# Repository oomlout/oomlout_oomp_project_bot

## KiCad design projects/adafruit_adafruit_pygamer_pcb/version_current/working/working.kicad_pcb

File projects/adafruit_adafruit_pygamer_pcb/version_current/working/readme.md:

# OOMP Project  
## Adafruit-PyGamer-PCB  by adafruit  
  
oomp key: oomp_projects_flat_adafruit_adafruit_pygamer_pcb  
(snippet of original readme)  
  
- Adafruit-PyGamer-PCB  
PCB files for Adafruit PyGamer  
  
Format is EagleCAD schematic and board layout  
  
For more details, check out the product page at  
  
   * https://www.adafruit.com/product/4242  
  
Adafruit invests time and resources providing this open source design,   
please support Adafruit and open-source hardware by purchasing   
products from Adafruit!  
  
Designed by Adafruit Industries.    
Creative Commons Attribution, Share-Alike license, check license.txt for more information  
All text above must be included in any redistribution  
  
  full source readme at [readme_src.md](readme_src.md)  
  
source repo at: [https://github.com/adafruit/Adafruit-PyGamer-PCB](https://github.com/adafruit/Adafruit-PyGamer-PCB)  
## Board  

## Schematic  

[schematic pdf](working_schematic.pdf)  
## Images

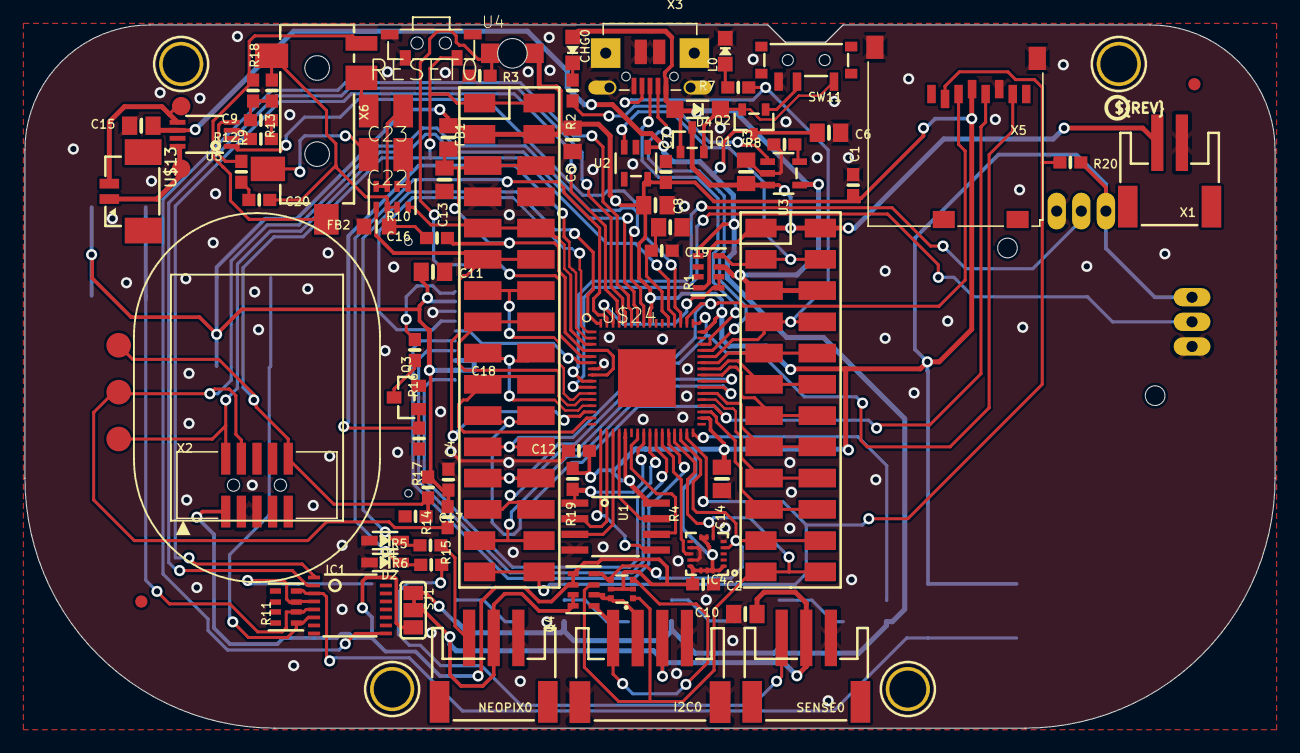
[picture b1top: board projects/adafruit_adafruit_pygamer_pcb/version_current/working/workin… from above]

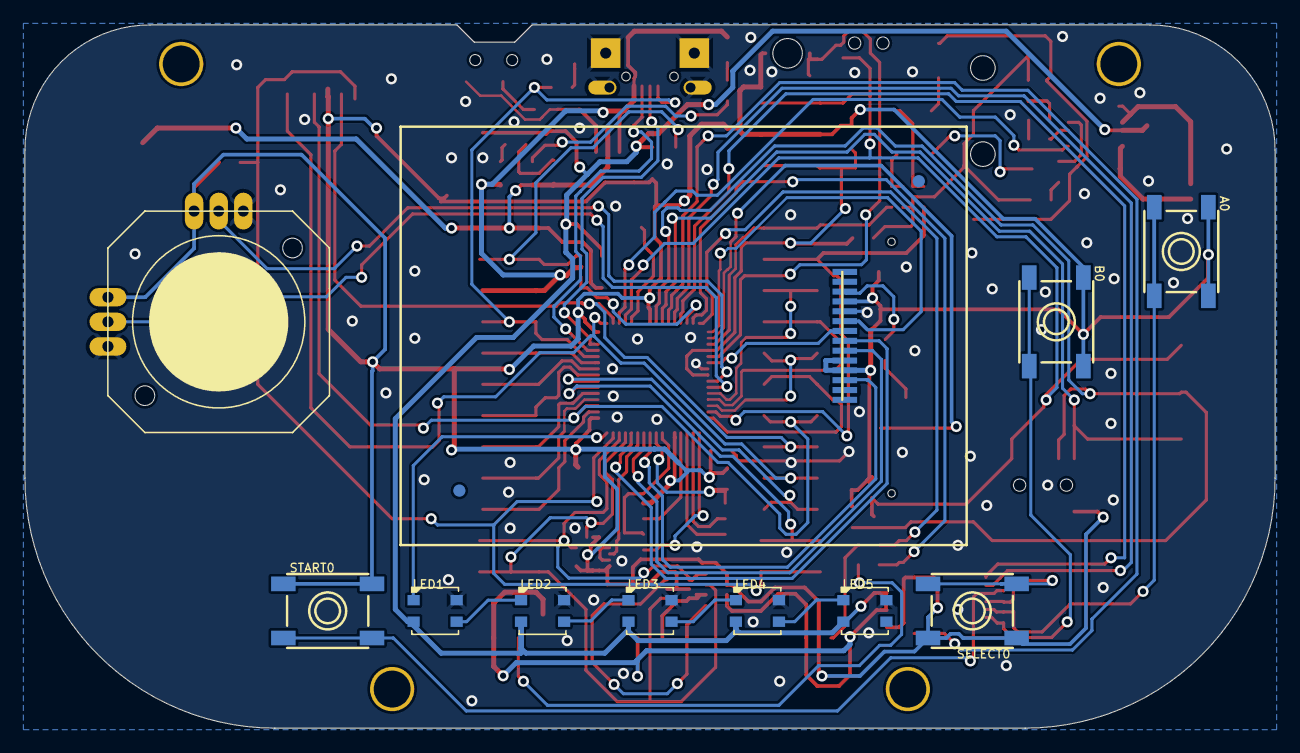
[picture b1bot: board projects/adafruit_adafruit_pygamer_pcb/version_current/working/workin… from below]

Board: 2 copper layers, 101.6 x 57.1 mm, 102 parts (14 on the bottom side), 92 nets.

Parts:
A0: 6MM_SMT_6MMCAP
B0: 6MM_SMT_6MMCAP
C1, C2, C4, C7, C9, C12, C16, C19, C20: 1uF; 0603-NO
C3, C6, C8: 10µF; 0805-NO
C5, C10, C11, C13, C14, C15, C18: 10uF; 0805-NO
C17: 0.1uF; 0603-NO
C22, C23: 100uF; C1210
CHG0: ORANGE; CHIPLED_0805_NOOUTLINE
D1, D2: 3.6V; SOD-323
D4: MBR0540; SOD-123
FB1: Ferrite; 0805-NO
FB2: Ferrite; _0805MP
I2C0: JST PH 4; JSTPH4
IC1: 74165TSSOP; TSSOP16
IC4: LIS3DH; LGA16_3X3MM
JOY1: JOYSTICK_ANALOG_XY; JOYSTICK_ANALOG_MINITHM
L0: RED; CHIPLED_0805_NOOUTLINE
LCD1: DISP_LCD_JDT1800; JD-T1800
LED1, LED2, LED3, LED4, LED5: WS2812B3535; LED3535
MS1: FEATHERWING_SMTDUALNOHOLES; FEATHERWING_SMT_NOHOLES
NEOPIX0: JST PH 3; JSTPH3
Q1, Q2: DMG2305; SOT23-R
Q3: BSS138; SOT23-WIDE
Q4: BSS138; SOT363
R1, R11: 100K; RESPACK_4X0603
R2, R5, R6: 1K; 0603-NO
R3, R14, R15, R20: 10K; 0603-NO
R4: 10K; RESPACK_4X0603
R7, R13, R18: 2.2K; 0603-NO
R8: 4.7K; 0603-NO
R9, R12: 100; 0603-NO
R10: 100; RESPACK_4X0603
R16: 10; 0603-NO
R17, R19: 100K; 0603-NO
RESET0: SPST_TACTILE_RA
SELECT0: 6MM_SMT_6MMCAP
SENSE0: JST PH 3; JSTPH3
SJ1: SOLDERJUMPER_2WAY_OPEN_NOPASTE
START0: 6MM_SMT_6MMCAP
SW11: SPDT_SMT_SSSS811101
TP1, TP2: TESTPOINT_ROUND_1.5MM_NO
TP6, TP7, TP8: TESTPOINT_ROUND_2MM_NO
U1: GD25Q64; SOIC8_208MIL
U2: AP2112-3.3; SOT23-5
U3: MCP73831T-2ACI/OT; SOT23-5
U4: ALS-PT21; ALS-PT26-21C
U5: PAM8302AASCR; MSOP8_0.65MM
U$5, U$6, U$17, U$18: MOUNTINGHOLE3.0THIN; MOUNTINGHOLE_3.0_PLATEDTHIN
U$8: SPEAKER_OVAL8OHM
U$13: CON_MOLEX_2P; 53398-0271
U$24: ATSAMD51J19; PQFN64-1
U$34, U$35, U$43, U$46: FIDUCIAL_1MM
U$37: PCBFEAT-REV-040
U$47: PYGAMER_BACK
U$48: PYGAMER_FRONT
X1: JSTPH; JSTPH2
X2: 2x5 0.05" SWD; 2X05_1.27MM_BOX_POSTS
X3: microUSB; 4UCONN_20329_V2
X5: MicroSD; MICROSD
X6: 4UCONN_19269

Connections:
+3V3: A0.B, A0.B', B0.B, B0.B', C1.1, C2.1, C4.1, C5.1, C7.1, C8.1, C11.1, C12.1, C14.1, FB1.1, IC1.16, IC4.1, IC4.7, IC4.8, IC4.13, IC4.14, IC4.15, IC4.16, JOY1.X+, JOY1.Y+, LCD1.4, LCD1.10, LCD1.11, MS1.2, MS1.2B, Q4.2, Q4.5, R4.1, R4.2, R14.1, R15.1, R19.1, R20.2, SELECT0.B, SELECT0.B', SJ1.3, START0.B, START0.B', U1.8, U2.5, U4.2_C, U$24.21, U$24.34, U$24.48, U$24.56, X2.1, X5.4
A0: MS1.5, MS1.5B, R10.8, U$24.3
A1: MS1.6, MS1.6B, R10.5, U$24.14
A2: MS1.7, MS1.7B, U$24.11
A3: MS1.8, MS1.8B, U$24.12
A4: MS1.9, MS1.9B, U$24.13
A5: MS1.10, MS1.10B, U$24.15
A6_VMEAS: R1.1, R1.2, U$24.62
A7_LIGHT: R3.2, U4.1_E, U$24.5
AGND: C16.2, C20.2, FB2.1, R10.6, R10.7, R13.1, X6.1
AVCC: C13.1, C16.1, FB1.2, MS1.3, MS1.3B, U$24.4, U$24.8
BUTTON4: IC1.3, R11.4, START0.A, START0.A'
BUTTON5: IC1.4, R11.3, SELECT0.A, SELECT0.A'
BUTTON6: A0.A, A0.A', IC1.5, R11.2
BUTTON7: B0.A, B0.A', IC1.6, R11.1
BUTTON_CLK: IC1.2, U$24.60
BUTTON_LATCH: IC1.1, U$24.61
BUTTON_OUT: IC1.9, U$24.59
CHG_LED: R2.2, U3.1
CHG_RATE: R8.1, U3.5
D2_: NEOPIX0.3, R5.1
D2_A8: D1.C, R5.2, U$24.64
D3_: R6.1, SENSE0.3
D3_A9: D2.C, R6.2, U$24.63
D4_SDCS: MS1.16, MS1.16B, R20.1, U$24.31, X5.2
D5: MS1.19, MS1.19B, U$24.35
D6: MS1.20, MS1.20B, U$24.37
D7_LISIRQ: IC4.11, U$24.27
D8_NEOPIX: LED1.1, U$24.32
D9: MS1.21, MS1.21B, U$24.38
D10: MS1.22, MS1.22B, U$24.41
D11: MS1.23, MS1.23B, U$24.42
D12: MS1.24, MS1.24B, U$24.43
D13_JACDAC: MS1.25, MS1.25B, R7.1, U$24.44, X3.ID
D+: U$24.46, X3.D+
D-: U$24.45, X3.D-
EN: MS1.27, MS1.27B, R1.4, U2.3
GND: C1.2, C2.2, C3.2, C4.2, C5.2, C6.2, C7.2, C8.2, C10.2, C11.2, C12.2, C13.2, C14.2, C15.2, C17.1, C18.2, C19.2, D1.A, D2.A, FB2.2, I2C0.1, I2C0.NC1, I2C0.NC2, IC1.8, IC1.10, IC1.11, IC1.12, IC1.13, IC1.14, IC1.15, IC4.5, IC4.10, IC4.12, JOY1.X-, JOY1.Y-, L0.C, LCD1.2, LCD1.5, LCD1.13, LED1.4, LED2.4, LED3.4, LED4.4, LED5.4, MS1.4, MS1.4B, NEOPIX0.1, Q3.2, R1.6, R1.7, R3.1, R8.2, R11.5, R11.6, R11.7, R11.8, R17.2, RESET0.2, RESET0.MT1, RESET0.MT2, SENSE0.1, SW11.C, U1.4, U2.2, U3.2, U5.7, U$24.7, U$24.22, U$24.33, U$24.47, U$24.54, U$24.EXP, X1.1, X2.3, X2.5, X3.BASE@1, X3.BASE@2, X3.GND, X3.SPRT@1, X3.SPRT@2, X3.SPRT@3, X3.SPRT@4, X5.6, X5.MT1, X5.MT2
JOYX: JOY1.X, U$24.10
JOYY: JOY1.Y, U$24.9
LEDK: LCD1.3, R16.1
MISO: MS1.13, MS1.13B, U$24.49, X5.7
MOSI: MS1.12, MS1.12B, U$24.50, X5.3
unnamed: CHG0.C, R2.1
unnamed: L0.A, R7.2
unnamed: LED1.3, LED2.1
unnamed: LED2.3, LED3.1
unnamed: LED3.3, LED4.1
unnamed: Q3.3, R16.2
unnamed: LED4.3, LED5.1
unnamed: D4.C, Q1.2, Q2.2, SW11.A
unnamed: R9.2, U5.4
unnamed: R12.2, U5.3
unnamed: C23.2, X6.3
unnamed: C9.2, R13.2, R18.1
unnamed: C22.2, X6.2
unnamed: C23.1, R10.3, R10.4
unnamed: C20.1, R9.1
unnamed: C9.1, R12.1
unnamed: C22.1, R10.1, R10.2
ON/OFF: Q2.1, SW11.B
QSPI_CS: R19.2, U1.1, U$24.24
QSPI_DATA[0]: U1.5, U$24.17
QSPI_DATA[1]: U1.2, U$24.18
QSPI_DATA[2]: U1.3, U$24.19
QSPI_DATA[3]: U1.7, U$24.20
QSPI_SCK: U1.6, U$24.23
RX: MS1.14, MS1.14B, U$24.40
SCK: MS1.11, MS1.11B, U$24.36, X5.5
SCL: I2C0.4, Q4.3, R4.5
SCL_3V: IC4.4, MS1.18, MS1.18B, Q4.4, R4.8, U$24.30
SDA: I2C0.3, Q4.6, R4.6
SDA_3V: IC4.6, MS1.17, MS1.17B, Q4.1, R4.7, U$24.29
SPEAKER_IN: R18.2, X6.4, X6.5
SPKR+: TP1.P$1, U5.5, U$13.2
SPKR-: TP2.P$1, U5.8, U$13.1
SPKR_EN: U5.1, U$24.51
SWCLK: R15.2, TP6.P$1, U$24.57, X2.4
SWDIO: TP7.P$1, U$24.58, X2.2
TFT_CS: LCD1.12, U$24.25
TFT_DC: LCD1.7, U$24.6
TFT_LITE: Q3.1, R17.1, U$24.2
TFT_MOSI: LCD1.8, U$24.28
TFT_RST: LCD1.6, U$24.1
TFT_SCK: LCD1.9, U$24.26
TX: MS1.15, MS1.15B, U$24.39
V+: C6.1, C15.1, LED1.2, LED2.2, LED3.2, LED4.2, LED5.2, Q2.3, R1.5, SJ1.1, U2.1, U5.6
VBAT: C3.1, MS1.28, MS1.28B, Q1.3, R1.8, U3.3, X1.2
VBUS: CHG0.A, D4.A, MS1.26, MS1.26B, Q1.1, R1.3, U3.4, X3.VBUS
VCC: C10.1, I2C0.2, NEOPIX0.2, R4.3, R4.4, SENSE0.2, SJ1.2
VDDCORE2: C18.1, C19.1, U$24.53
~RESET: C17.2, MS1.1, MS1.1B, R14.2, RESET0.1, TP8.P$1, U$24.52, X2.10

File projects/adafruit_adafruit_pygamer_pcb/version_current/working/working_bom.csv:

"Id";"Designator";"Footprint";"Quantity";"Designation";"Supplier and ref";
1;"C11,C13,C5,C10,C15,C14,C18";"0805-NO";7;"10uF";;;
2;"C12,C4,C2,C20,C16,C19,C9,C7,C1";"0603-NO";9;"1uF";;;
3;"R3,R14,R15,R20";"0603-NO";4;"10K";;;
4;"IC4";"LGA16_3X3MM";1;"LIS3DH";;;
5;"R8";"0603-NO";1;"4.7K";;;
6;"FB2";"_0805MP";1;"Ferrite";;;
7;"U$24";"PQFN64-1";1;"ATSAMD51J19";;;
8;"IC1";"TSSOP16";1;"74165TSSOP";;;
9;"SENSE0,NEOPIX0";"JSTPH3";2;"JST PH 3";;;
10;"C22,C23";"C1210";2;"100uF";;;
11;"R17,R19";"0603-NO";2;"100K";;;
12;"Q2,Q1";"SOT23-R";2;"DMG2305";;;
13;"R13,R7,R18";"0603-NO";3;"2.2K";;;
14;"U$13";"53398-0271";1;"CON_MOLEX_2P";;;
15;"FB1";"0805-NO";1;"Ferrite";;;
16;"U2";"SOT23-5";1;"AP2112-3.3";;;
17;"U$47";"PYGAMER_BACK";1;"";;;
18;"TP7,TP6,TP8";"TESTPOINT_ROUND_2MM_NO";3;"";;;
19;"R10";"RESPACK_4X0603";1;"100";;;
20;"R9,R12";"0603-NO";2;"100";;;
21;"D1,D2";"SOD-323";2;"3.6V";;;
22;"I2C0";"JSTPH4";1;"JST PH 4";;;
23;"Q4";"SOT363";1;"BSS138";;;
24;"D4";"SOD-123";1;"MBR0540";;;
25;"C3,C8,C6";"0805-NO";3;"10µF";;;
26;"U$35,U$34,U$43,U$46";"FIDUCIAL_1MM";4;"FIDUCIAL_1MM";;;
27;"X2";"2X05_1.27MM_BOX_POSTS";1;"2x5 0.05" SWD";;;
28;"R2,R5,R6";"0603-NO";3;"1K";;;
29;"U4";"ALS-PT26-21C";1;"ALS-PT21";;;
30;"L0";"CHIPLED_0805_NOOUTLINE";1;"RED";;;
31;"TP2,TP1";"TESTPOINT_ROUND_1.5MM_NO";2;"";;;
32;"C17";"0603-NO";1;"0.1uF";;;
33;"U5";"MSOP8_0.65MM";1;"PAM8302AASCR";;;
34;"U$6,U$18,U$5,U$17";"MOUNTINGHOLE_3.0_PLATEDTHIN";4;"MOUNTINGHOLE3.0THIN";;;
35;"U1";"SOIC8_208MIL";1;"GD25Q64";;;
36;"SJ1";"SOLDERJUMPER_2WAY_OPEN_NOPASTE";1;"";;;
37;"U$8";"SPEAKER_OVAL8OHM";1;"";;;
38;"X3";"4UCONN_20329_V2";1;"microUSB";;;
39;"SW11";"SPDT_SMT_SSSS811101";1;"";;;
40;"MS1";"FEATHERWING_SMT_NOHOLES";1;"FEATHERWING_SMTDUALNOHOLES";;;
41;"R16";"0603-NO";1;"10";;;
42;"X6";"4UCONN_19269";1;"";;;
43;"X5";"MICROSD";1;"MicroSD";;;
44;"R1,R11";"RESPACK_4X0603";2;"100K";;;
45;"RESET0";"SPST_TACTILE_RA";1;"";;;
46;"X1";"JSTPH2";1;"JSTPH";;;
47;"U3";"SOT23-5";1;"MCP73831T-2ACI/OT";;;
48;"CHG0";"CHIPLED_0805_NOOUTLINE";1;"ORANGE";;;
49;"U$37";"PCBFEAT-REV-040";1;"";;;
50;"Q3";"SOT23-WIDE";1;"BSS138";;;
51;"R4";"RESPACK_4X0603";1;"10K";;;
52;"START0,SELECT0,B0,A0";"6MM_SMT_6MMCAP";4;"";;;
53;"LED5,LED2,LED1,LED3,LED4";"LED3535";5;"WS2812B3535";;;
54;"LCD1";"JD-T1800";1;"DISP_LCD_JDT1800";;;
55;"JOY1";"JOYSTICK_ANALOG_MINITHM";1;"JOYSTICK_ANALOG_XY";;;
56;"U$48";"PYGAMER_FRONT";1;"";;;

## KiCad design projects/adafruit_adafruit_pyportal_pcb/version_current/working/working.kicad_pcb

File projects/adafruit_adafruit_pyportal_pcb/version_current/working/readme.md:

# Adafruit-PyPortal-PCB by adafruit  
This is a harvested standardized copy of a project from github.  
The original project can be found at:  
https://github.com/adafruit/Adafruit-PyPortal-PCB  
Please consult that link for additional, details, files, and license information.  
Note: It was auto harvested and if the original repo had more than one board file or anything out of the ordinary the files here are likely not representative.

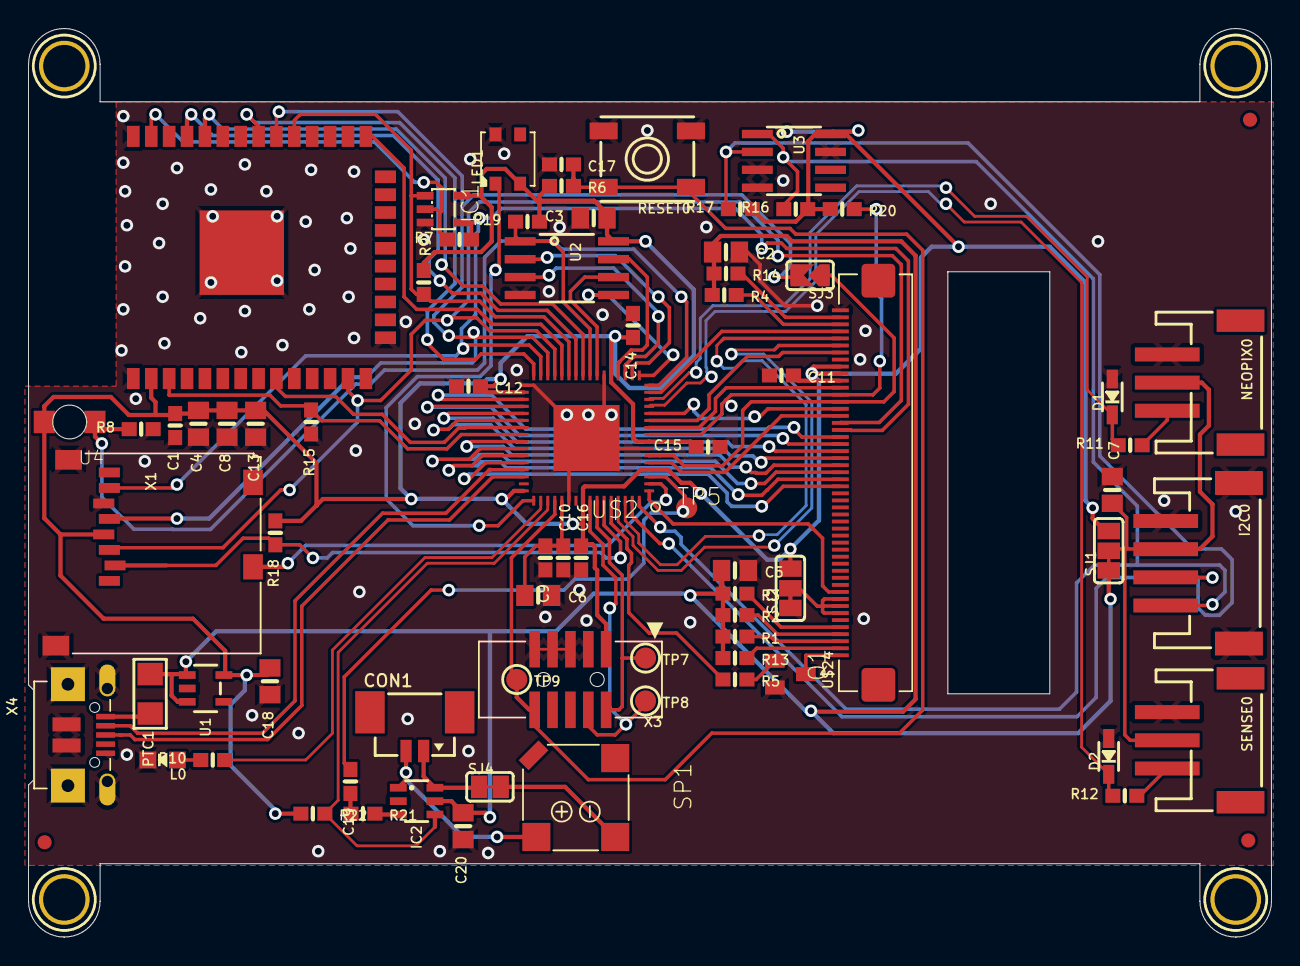
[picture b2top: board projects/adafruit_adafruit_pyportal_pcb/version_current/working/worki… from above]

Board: 16 copper layers, 88.3 x 64.5 mm, 81 parts (1 on the bottom side), 75 nets.

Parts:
C1, C17, C19: 0.1uF; 0603-NO
C2, C3, C5, C6, C7, C8, C13, C18, C20: 10uF; 0805-NO
C4: 0.1uF; 0805-NO
C9: 1uF; 0603-NO
C10, C11, C12, C14, C15, C16: .1u; 0603-NO
CON1: CON_MOLEX_2P; 53398-0271
D1, D2: 3.6V; SOD-323
I2C0: JST PH 4; JSTPH4
IC1: 74AHC1G125; SOT23-5L
IC2: PAM8301; SOT23-6
L0: RED; CHIPLED_0805_NOOUTLINE
LED1: WS2812B3535; LED3535
NEOPIX0: JST PH 3; JSTPH3
PTC1: 500mA; 1206
Q1: MMBT2222; SOT23-BEC
R1, R2, R3, R4, R13, R14: 100; 0603-NO
R5, R10, R11, R12: 1K; 0603-NO
R6, R8, R9, R15, R16, R17, R18, R19, R20: 10K; 0603-NO
R7: DNP; 0603-NO
R21, R22: 47K; 0603-NO
RESET0: EVQQ 6mm; EVQ-Q2_SMALLER
SENSE0: JST PH 3; JSTPH3
SJ1, SJ2: SOLDERJUMPER_2WAY_OPEN_NOPASTE
SJ3: SOLDERJUMPER_ARROW_NOPASTE
SJ4: SOLDERJUMPER_CLOSEDWIRE
SP1: 7.5mm SPK; BUZZER_SMT_7.5MM
TP5: TPTP15R; TP15R
TP7, TP8, TP9: TESTPOINT_ROUND_1.5MM
U1: AP2112-3.3; SOT23-5
U2: GD25Q64; SOIC8_208MIL
U3: ADT7410; SOIC8_150MIL
U4: ALS-PT21; ALS-PT26-21C
U$2: ATSAMD51J20; PQFN64-1
U$7, U$15, U$16, U$17: MOUNTINGHOLE3.0THIN; MOUNTINGHOLE_3.0_PLATEDTHIN
U$9, U$11, U$23: FIDUCIAL_1MM
U$24: DISP_LCD_6LED_240X320_50PIN; TFT_3.2IN_240X320_50PIN
X1: microSD; MICROSD
X3: 2x5 0.05" SWD; 2X05_1.27MM_BOX_POSTS
X4: microUSB; 4UCONN_20329_V2
X6: ESP32_WROOM32; WROOM32

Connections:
3.3V: C1.1, C3.1, C4.1, C8.1, C11.2, C12.2, C13.1, C14.2, C15.2, C16.2, C18.1, IC1.5, LED1.2, R6.1, R9.2, R16.1, R17.1, R18.1, R19.1, R20.1, R22.1, SJ1.3, SJ2.3, U1.5, U2.8, U3.8, U4.2_C, U$2.4, U$2.8, U$2.21, U$2.34, U$2.48, U$2.56, U$24.40, U$24.41, U$24.42, X1.4, X3.1, X6.2
+5V: C2.1, C5.1, C20.1, IC2.5, PTC1.1, R1.1, R2.1, R3.1, R4.1, R13.1, R14.1, SJ1.1, U1.1, U1.3
AUDIO_OUT: C19.1, TP5.TP, U$2.3
CARDDET: U$2.2, X1.CD2
D3: R12.1, SENSE0.3
D3_UNSAFE: D2.C, R12.2, U$2.13
D4: NEOPIX0.3, R11.1
D4_UNSAFE: D1.C, R11.2, U$2.14
D13: R10.1, U$2.50
D+: U$2.46, X4.D+
D-: U$2.45, X4.D-
ESP_BUSY: U$2.39, X6.9
ESP_CS: IC1.1, R9.1, U$2.27, X6.29
ESP_GPIO0: U$2.28, X6.25
ESP_MISO: IC1.2, R7.2, X6.37
ESP_RESET: R15.1, U$2.40, X6.3
ESP_RTS: U$2.32, X6.31
GND: C1.2, C2.2, C3.2, C4.2, C5.2, C6.2, C7.2, C8.2, C9.2, C10.1, C11.1, C12.1, C13.2, C14.1, C15.1, C16.1, C17.1, C18.2, C20.2, D1.A, D2.A, I2C0.1, I2C0.NC1, I2C0.NC2, IC1.3, IC2.2, L0.C, LED1.4, NEOPIX0.1, Q1.E, R8.1, R15.2, RESET0.A, RESET0.A', SENSE0.1, SJ2.1, U1.2, U2.4, U3.3, U3.4, U3.7, U$2.7, U$2.22, U$2.33, U$2.47, U$2.54, U$2.EXP, U$24.6, U$24.43, U$24.50, X1.6, X1.MT1, X1.MT2, X3.3, X3.5, X3.7, X3.9, X4.BASE@1, X4.BASE@2, X4.GND, X4.SPRT@1, X4.SPRT@2, X4.SPRT@3, X4.SPRT@4, X6.1, X6.15, X6.38, X6.P$1
LCD_DATA0: U$2.35, U$24.32
LCD_DATA1: U$2.36, U$24.31
LCD_DATA2: U$2.37, U$24.30
LCD_DATA3: U$2.38, U$24.29
LCD_DATA4: U$2.41, U$24.28
LCD_DATA5: U$2.42, U$24.27
LCD_DATA6: U$2.43, U$24.26
LCD_DATA7: U$2.44, U$24.25
LEDK: Q1.C, U$24.1
LIGHT: R8.2, U4.1_E, U$2.16
MISO: IC1.4, R7.1, U$2.31, U$24.33, X1.7
MOSI: U$2.29, U$24.34, X1.3, X6.13
unnamed: R4.2, U$24.48
unnamed: R1.2, U$24.3
unnamed: R2.2, U$24.4
unnamed: R3.2, U$24.5
unnamed: SJ2.2, U$24.7, U$24.8, U$24.9
unnamed: R14.2, U$24.49
unnamed: R13.2, U$24.2
unnamed: L0.A, R10.2
unnamed: C19.2, R21.1
unnamed: IC2.3, R21.2
unnamed: SJ4.2, SP1.-
unnamed: Q1.B, R5.2
NEOPIX: LED1.1, U$2.49
QSPI_CS: R19.2, U2.1, U$2.24
QSPI_DATA[0]: U2.5, U$2.17
QSPI_DATA[1]: U2.2, U$2.18
QSPI_DATA[2]: U2.3, U$2.19
QSPI_DATA[3]: U2.7, U$2.20
QSPI_SCK: U2.6, U$2.23
RXD: U$2.26, X6.35
SCK: SJ3.2, U$2.30, X1.5, X6.30
SCL: I2C0.4, R16.2, U3.1, U$2.64
SDA: I2C0.3, R17.2, U3.2, U$2.63
SD_CS: R18.2, U$2.59, X1.2
SPKR+: CON1.2, IC2.1, SP1.+
SPK_SD: IC2.4, R22.2, U$2.51
SPRK-: CON1.1, IC2.6, SJ4.1
SWCLK: TP8.P$1, U$2.57, X3.4
SWDIO: TP7.P$1, U$2.58, X3.2
TFT_BACKLITE: R5.1, U$2.60
TFT_CS: R20.2, U$2.9, U$24.38
TFT_RD: U$2.5, U$24.35
TFT_RESET: U$2.1, U$24.10
TFT_RS: SJ3.1, U$2.6, U$24.37
TFT_TE: U$2.10, U$24.39
TFT_WR: U$2.12, U$24.36
TOUCH_XL: U$2.62, U$24.46
TOUCH_XR: U$2.11, U$24.44
TOUCH_YD: U$2.61, U$24.45
TOUCH_YU: U$2.15, U$24.47
TXD: U$2.25, X6.34
VBUS: PTC1.2, X4.VBUS
VCC: C7.1, I2C0.2, NEOPIX0.2, SENSE0.2, SJ1.2
VDDCORE: C6.1, C9.1, C10.2, U$2.53
~RESET: C17.2, R6.2, RESET0.B, RESET0.B', TP9.P$1, U$2.52, X3.10

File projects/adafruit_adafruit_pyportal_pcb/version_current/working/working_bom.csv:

"Id";"Designator";"Footprint";"Quantity";"Designation";"Supplier and ref";
1;"IC2";"SOT23-6";1;"PAM8301";;;
2;"C7,C5,C8,C3,C13,C18,C6,C20,C2";"0805-NO";9;"10uF";;;
3;"SP1";"BUZZER_SMT_7.5MM";1;"7.5mm SPK";;;
4;"C12,C14,C11,C10,C15,C16";"0603-NO";6;".1u";;;
5;"R8,R15,R20,R19,R6,R9,R17,R16,R18";"0603-NO";9;"10K";;;
6;"TP8,TP7,TP9";"TESTPOINT_ROUND_1.5MM";3;"";;;
7;"NEOPIX0,SENSE0";"JSTPH3";2;"JST PH 3";;;
8;"C9";"0603-NO";1;"1uF";;;
9;"R2,R4,R14,R13,R3,R1";"0603-NO";6;"100";;;
10;"L0";"CHIPLED_0805_NOOUTLINE";1;"RED";;;
11;"C4";"0805-NO";1;"0.1uF";;;
12;"U$17,U$15,U$16,U$7";"MOUNTINGHOLE_3.0_PLATEDTHIN";4;"MOUNTINGHOLE3.0THIN";;;
13;"I2C0";"JSTPH4";1;"JST PH 4";;;
14;"D1,D2";"SOD-323";2;"3.6V";;;
15;"X6";"WROOM32";1;"ESP32_WROOM32";;;
16;"C17,C19,C1";"0603-NO";3;"0.1uF";;;
17;"U$11,U$23,U$9";"FIDUCIAL_1MM";3;"FIDUCIAL_1MM";;;
18;"U3";"SOIC8_150MIL";1;"ADT7410";;;
19;"R5,R11,R12,R10";"0603-NO";4;"1K";;;
20;"TP5";"TP15R";1;"TPTP15R";;;
21;"R7";"0603-NO";1;"DNP";;;
22;"RESET0";"EVQ-Q2_SMALLER";1;"EVQQ 6mm";;;
23;"X1";"MICROSD";1;"microSD";;;
24;"U$2";"PQFN64-1";1;"ATSAMD51J20";;;
25;"SJ4";"SOLDERJUMPER_CLOSEDWIRE";1;"";;;
26;"X3";"2X05_1.27MM_BOX_POSTS";1;"2x5 0.05" SWD";;;
27;"R21,R22";"0603-NO";2;"47K";;;
28;"SJ3";"SOLDERJUMPER_ARROW_NOPASTE";1;"";;;
29;"CON1";"53398-0271";1;"CON_MOLEX_2P";;;
30;"SJ2,SJ1";"SOLDERJUMPER_2WAY_OPEN_NOPASTE";2;"";;;
31;"U2";"SOIC8_208MIL";1;"GD25Q64";;;
32;"Q1";"SOT23-BEC";1;"MMBT2222";;;
33;"PTC1";"1206";1;"500mA";;;
34;"X4";"4UCONN_20329_V2";1;"microUSB";;;
35;"U1";"SOT23-5";1;"AP2112-3.3";;;
36;"LED1";"LED3535";1;"WS2812B3535";;;
37;"IC1";"SOT23-5L";1;"74AHC1G125";;;
38;"U4";"ALS-PT26-21C";1;"ALS-PT21";;;
39;"U$24";"TFT_3.2IN_240X320_50PIN";1;"DISP_LCD_6LED_240X320_50PIN";;;

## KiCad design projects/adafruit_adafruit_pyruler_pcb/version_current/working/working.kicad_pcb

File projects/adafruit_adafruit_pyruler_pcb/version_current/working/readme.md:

# Adafruit-PyRuler-PCB by adafruit  
This is a harvested standardized copy of a project from github.  
The original project can be found at:  
https://github.com/adafruit/Adafruit-PyRuler-PCB  
Please consult that link for additional, details, files, and license information.  
Note: It was auto harvested and if the original repo had more than one board file or anything out of the ordinary the files here are likely not representative.

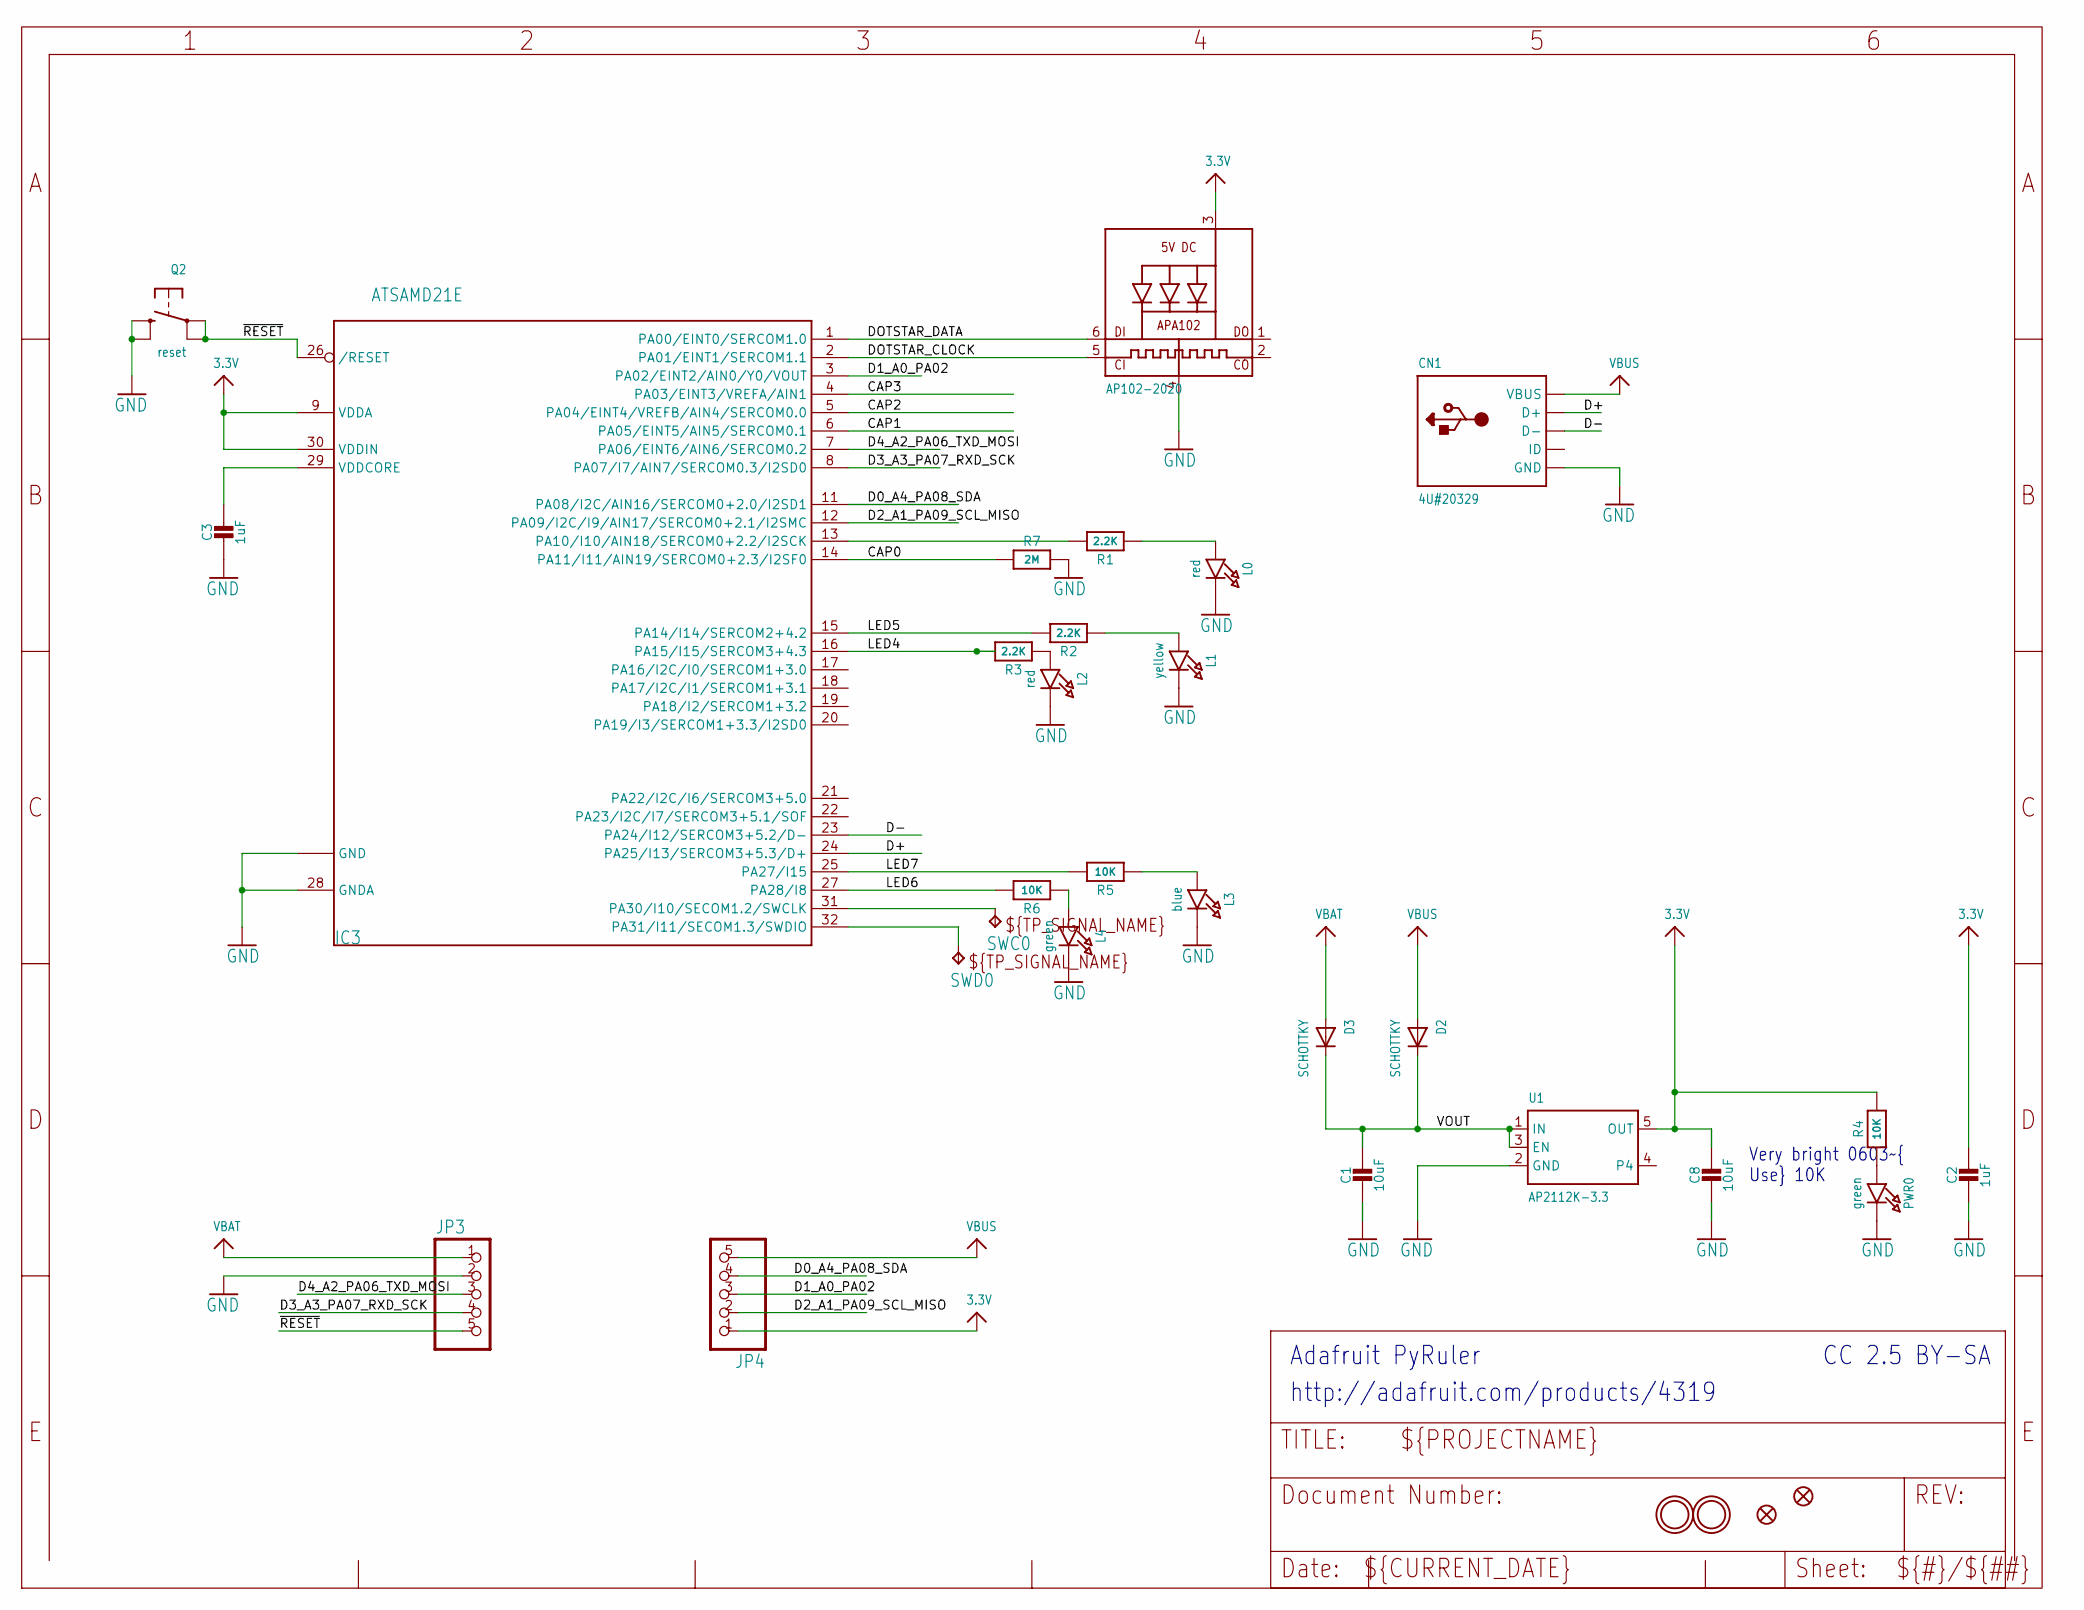
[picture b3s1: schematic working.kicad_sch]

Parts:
C1, C8: 10uF; 0805-NO
C2, C3: 1uF; 0603-NO
CN1: 4U#20329; 4UCONN_20329_NARROW
D2, D3: SCHOTTKY; SOD-123FL
IC3: ATSAMD21E; QFN32_5MM
JP3, JP4: HEADER-1X570MIL; 1X05_ROUND_70
L0, L2: red; CHIPLED_0603_NOOUTLINE
L1: yellow; CHIPLED_0603_NOOUTLINE
L3: blue; CHIPLED_0603_NOOUTLINE
L4: green; CHIPLED_0603_NOOUTLINE
LED1: AP102-2020; APA102_2020
PWR0: green; CHIPLED_0603_NOOUTLINE
Q2: reset; BTN_KMR2_4.6X2.8
R1, R2, R3: 2.2K; 0603-NO
R4, R5, R6: 10K; 0603-NO
R7: 2M; 0603-NO
SWC0: TPB1,27; B1,27
SWD0: TPB1,27; B1,27
U1: AP2112K-3.3; SOT23-5
U$1, U$6: FIDUCIAL_1MM
U$8, U$9: MOUNTINGHOLE2.0; MOUNTINGHOLE_2.0_PLATED

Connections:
3.3V: C2.1, C8.1, IC3.9 (VDDA), IC3.30 (VDDIN), JP4.1, LED1.3 (VDD), R4.2, U1.5 (OUT)
CAP0: IC3.14 (PA11/I11/AIN19/SERCOM0+2.3/I2SF0), R7.1
CAP1: IC3.6 (PA05/EINT5/AIN5/SERCOM0.1)
CAP2: IC3.5 (PA04/EINT4/VREFB/AIN4/SERCOM0.0)
CAP3: IC3.4 (PA03/EINT3/VREFA/AIN1)
D0_A4_PA08_SDA: IC3.11 (PA08/I2C/AIN16/SERCOM0+2.0/I2SD1), JP4.4
D1_A0_PA02: IC3.3 (PA02/EINT2/AIN0/Y0/VOUT), JP4.3
D2_A1_PA09_SCL_MISO: IC3.12 (PA09/I2C/I9/AIN17/SERCOM0+2.1/I2SMC), JP4.2
D3_A3_PA07_RXD_SCK: IC3.8 (PA07/I7/AIN7/SERCOM0.3/I2SD0), JP3.4
D4_A2_PA06_TXD_MOSI: IC3.7 (PA06/EINT6/AIN6/SERCOM0.2), JP3.3
D+: CN1.D+, IC3.24 (PA25/I13/SERCOM3+5.3/D+)
D-: CN1.D-, IC3.23 (PA24/I12/SERCOM3+5.2/D-)
DOTSTAR_CLOCK: IC3.2 (PA01/EINT1/SERCOM1.1), LED1.5 (CKI)
DOTSTAR_DATA: IC3.1 (PA00/EINT0/SERCOM1.0), LED1.6 (DI)
GND: C1.2, C2.2, C3.2, C8.2, CN1.BASE@1 (GND), CN1.BASE@2 (GND), CN1.GND, CN1.SPRT@1 (GND), CN1.SPRT@2 (GND), CN1.SPRT@3 (GND), CN1.SPRT@4 (GND), IC3.10 (GND), IC3.28 (GNDA), IC3.33 (GND), JP3.2, L0.C, L1.C, L2.C, L3.C, L4.C, LED1.4 (GND), PWR0.C, Q2.B (S), Q2.B' (S1), R7.2, U1.2 (GND)
LED: IC3.13 (PA10/I10/AIN18/SERCOM0+2.2/I2SCK), R1.2
LED4: IC3.16 (PA15/I15/SERCOM3+4.3), R3.2
LED5: IC3.15 (PA14/I14/SERCOM2+4.2), R2.2
LED6: IC3.27 (PA28/I8), R6.2
LED7: IC3.25 (PA27/I15), R5.2
unnamed: L0.A, R1.1
unnamed: IC3.31 (PA30/I10/SECOM1.2/SWCLK), SWC0.TP
unnamed: IC3.32 (PA31/I11/SECOM1.3/SWDIO), SWD0.TP
unnamed: PWR0.A, R4.1
unnamed: L1.A, R2.1
unnamed: L2.A, R3.1
unnamed: L4.A, R6.1
unnamed: L3.A, R5.1
VBAT: D3.A, JP3.1
VBUS: CN1.VBUS, D2.A, JP4.5
VDDCORE: C3.1, IC3.29 (VDDCORE)
VOUT: C1.1, D2.C, D3.C, U1.1 (IN), U1.3 (EN)
~RESET: IC3.26 (/RESET), JP3.5, Q2.A, Q2.A' (P1)

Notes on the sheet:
CC 2.5 BY-SA
http://adafruit.com/products/4319
Adafruit PyRuler
Very bright 0603~{ Use} 10K

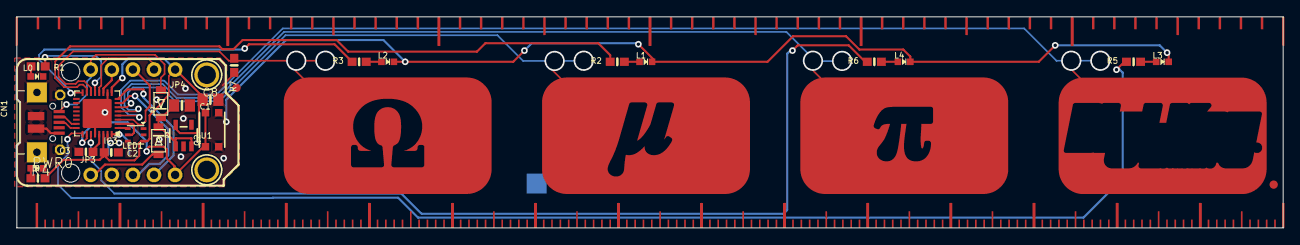
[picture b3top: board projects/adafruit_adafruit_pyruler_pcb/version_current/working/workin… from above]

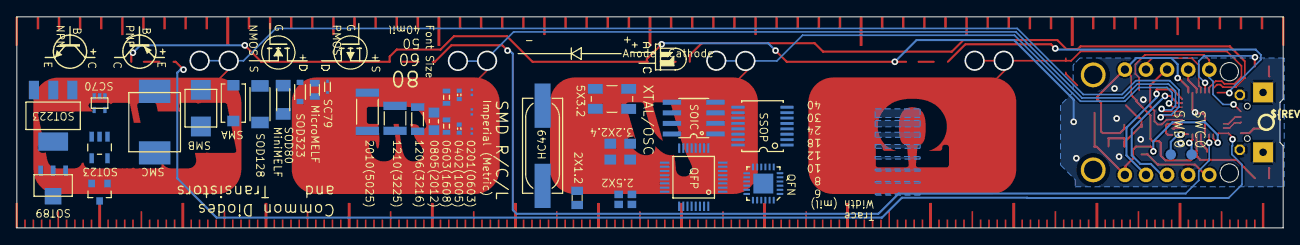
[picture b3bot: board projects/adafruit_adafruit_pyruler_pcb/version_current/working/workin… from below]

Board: 16 copper layers, 152.4 x 25.4 mm, 98 parts (43 on the bottom side), 30 nets.

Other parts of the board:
@HOLE0, @HOLE1: (no value)
E$1, E$2, E$3, E$4, E$5, E$6, E$7, E$8, E$9, E$10, E$11, E$12, E$13, E$14, E$15: EDGE-MILLIMETERS
E$16, E$60, E$63: 0201
E$17, E$18, E$19, E$20, E$21, E$22: EDGE-INCHES-TENTH
E$23, E$61: 0402
E$24, E$62: 0603
E$25: 0805
E$26: 1206
E$27: 1210
E$28: 2010
E$31: SOT223
E$32: SOT89
E$33: SOT23-5
E$34: SOT23-3
E$35: SC70
E$36: CRYSTAL-SMD-5X3.2
E$37: CRYSTAL-SMD-3.2X2.5
E$38: CRYSTAL-SMD-2.5X2
E$39: HC49UP
E$40: XTAL-2X1.2
E$41: MICROMELF-R
E$42: SC79_INFINEON
E$43: SMA-DIODE
E$44: SMB-DIODE
E$45: SMC
E$47: SOD-128
E$48: SOD-323
E$49: SOD80C
E$50: NMOS-SYMB
E$51: PMOS-SYMB
E$52: DIODE-SYMB
E$53: LED-GUIDE
E$54: NPN-SYMB
E$55: QFN-24
E$56: TSSOP16
E$57: SO08
E$58: TQFP32-5MM
E$59: PNP-SYMB
U$2: PYRULER_BOTTOM
U$7: PCBFEAT-REV-040
U$14: PYRULER_TOP
U$20: TRINKET_M0_TOP

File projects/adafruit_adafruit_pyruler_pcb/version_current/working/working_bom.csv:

Row,Description,Part,References,Value,Footprint,Quantity Per PCB,Status,Datasheet
1,,CAP_CERAMIC0603_NO,C2 C3,1uF,0603-NO,2, ,
2,,CAP_CERAMIC0805-NOOUTLINE,C1 C8,10uF,0805-NO,2, ,
3,,USB_MICRO_NARROW,CN1,4U#20329,4UCONN_20329_NARROW,1, ,
4,,DIODE_SOD-123FL,D2 D3,SCHOTTKY,SOD-123FL,2, ,
5,,ATSAMD21E,IC3,ATSAMD21E,QFN32_5MM,1, ,
6,,HEADER-1X570MIL,JP3 JP4,HEADER-1X570MIL,1X05_ROUND_70,2, ,
7,,LED0603_NOOUTLINE,L3,blue,CHIPLED_0603_NOOUTLINE,1, ,
8,,LED0603_NOOUTLINE,L4 PWR0,green,CHIPLED_0603_NOOUTLINE,2, ,
9,,LED0603_NOOUTLINE,L0 L2,red,CHIPLED_0603_NOOUTLINE,2, ,
10,,LED0603_NOOUTLINE,L1,yellow,CHIPLED_0603_NOOUTLINE,1, ,
11,,APA1022020,LED1,AP102-2020,APA102_2020,1, ,
12,,SWITCH_TACT_SMT4.6X2.8,Q2,reset,BTN_KMR2_4.6X2.8,1, ,
13,,RESISTOR_0603_NOOUT,R1 R2 R3,2.2K,0603-NO,3, ,
14,,RESISTOR_0603_NOOUT,R4 R5 R6,10K,0603-NO,3, ,
15,,RESISTOR_0603_NOOUT,R7,2M,0603-NO,1, ,
16,,"TPB1,27",SWC0 SWD0,"TPB1,27","B1,27",2, ,
17,,VREG_SOT23-5,U1,AP2112K-3.3,SOT23-5,1, ,





Project info:
Schematic:,working
Variant:,default
Revision:,
Date:,2023-08-03_17-21-23
KiCad Version:,7.0.6-7.0.6~ubuntu22.04.1
Statistics:
Component Groups:,17
Component Count:,28 (0 SMD/ 0 THT)
Fitted Components:,28 (0 SMD/ 0 THT)
Number of PCBs:,1
Total Components:,28

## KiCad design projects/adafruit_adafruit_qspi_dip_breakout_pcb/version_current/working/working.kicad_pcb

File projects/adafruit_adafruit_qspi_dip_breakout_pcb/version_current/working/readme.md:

# OOMP Project  
## Adafruit-QSPI-DIP-Breakout-PCB  by adafruit  
  
oomp key: oomp_projects_flat_adafruit_adafruit_qspi_dip_breakout_pcb  
(snippet of original readme)  
  
-- Adafruit QSPI DIP Breakout Board PCB  
  
<a href="http://www.adafruit.com/products/5632"><br/>  
Click here to purchase one from the Adafruit shop</a>  
  
<a href="http://www.adafruit.com/products/5633"><br/>  
Click here to purchase one from the Adafruit shop</a>  
  
<a href="http://www.adafruit.com/products/5634"><br/>  
Click here to purchase one from the Adafruit shop</a>  
  
PCB files for the Adafruit QSPI DIP Breakout Board.   
  
Format is EagleCAD schematic and board layout  
* https://www.adafruit.com/product/5632  
* https://www.adafruit.com/product/5633  
* https://www.adafruit.com/product/5634  
  
--- Description  
  
For many modern and powerful chips like the RP2040, ESP32, RT10xx and STM32 series microcontrollers, designers can save money and reduce the number of chip options by not including building in the Flash memory used to store code and resources. Instead, an external QSPI Flash memory chip is wired up that can provide 16-128 Megabytes of memory (5632 - 16MB, 5633 - 64MB, 5634 - 128MB. It's not as fast as if it were on the microcontroller internal bus but with Quad SPI I/O and some clever caching by the chip designer, it's pretty effective!  
  
To make prototyping and designing with QSPI flash a little easier, we designed these breakouts that convert the wide 8-SOIC packages to a cute 0.3" wide DIP. We find these handy when testing out diffe  
  full source readme at [readme_src.md](readme_src.md)  
  
source repo at: [https://github.com/adafruit/Adafruit-QSPI-DIP-Breakout-PCB](https://github.com/adafruit/Adafruit-QSPI-DIP-Breakout-PCB)  
## Board  

## Schematic  

[schematic pdf](working_schematic.pdf)  
## Images

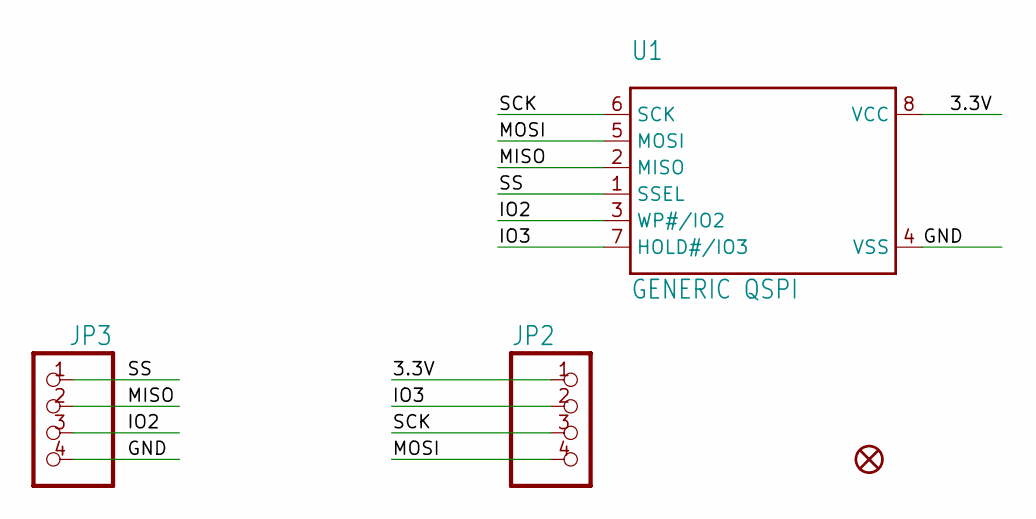
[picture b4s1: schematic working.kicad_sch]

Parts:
FID1: FIDUCIAL_1MM
JP2, JP3: HEADER-1X476MIL; 1X04_ROUND_76
U1: GENERIC QSPI; SOIC8_208MIL

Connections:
3.3V: JP2.1, U1.8 (VCC)
GND: JP3.4, U1.4 (VSS)
IO2: JP3.3, U1.3 (WP#/IO2)
IO3: JP2.2, U1.7 (HOLD#/IO3)
MISO: JP3.2, U1.2 (MISO)
MOSI: JP2.4, U1.5 (MOSI)
SCK: JP2.3, U1.6 (SCK)
SS: JP3.1, U1.1 (SSEL)

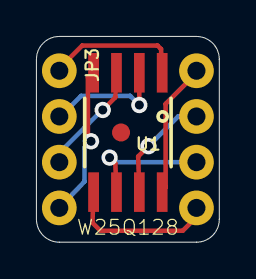
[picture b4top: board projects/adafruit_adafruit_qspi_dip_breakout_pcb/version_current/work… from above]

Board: 2 copper layers, 10.2 x 11.4 mm, 5 parts (1 on the bottom side), 8 nets.

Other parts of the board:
U$4: ADAFRUIT_2.5MM

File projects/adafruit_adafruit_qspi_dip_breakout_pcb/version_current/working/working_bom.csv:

Row,Description,Part,References,Value,Footprint,Quantity Per PCB,Status,Datasheet
1,,HEADER-1X476MIL,JP2 JP3,HEADER-1X476MIL,1X04_ROUND_76,2, ,
2,,SPIFLASH_8PIN208MIL,U1,GENERIC QSPI,SOIC8_208MIL,1, ,





Project info:
Schematic:,working
Variant:,default
Revision:,
Date:,2023-08-03_17-21-23
KiCad Version:,7.0.6-7.0.6~ubuntu22.04.1
Statistics:
Component Groups:,2
Component Count:,3 (0 SMD/ 0 THT)
Fitted Components:,3 (0 SMD/ 0 THT)
Number of PCBs:,1
Total Components:,3
